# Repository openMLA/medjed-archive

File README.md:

The **Medjed** maskless lithography aligner is part of the openMLA series of photolithography equipment. 

>  **🏗️ Construction in progress**
> A lot is still being worked on for this system. Hardware is being tested and performance will need to be evaluated before people will be able to build their own system. 

### Overview

The MEDJED system is a photolithography system - this means its primary function is to expose a (flat-ish) substrate to patterened light. The substrate will need to be coated in a layer of light-sensitive material known as photoresist. This resist layer in turn will undergo chemical reactions upon exposure to UV light, either rendering areas that were exposed soluble or insoluble to a (liquid) chemical developer. After development of the exposed photoresist layer, some areas of the substrate will remain coated in the photoresist, while others will be free of it. This is the starting point for further patterning steps and is the backbone of modern microfabrication.

The MEDJED system targets a 5um pixel size in its current design. The total project cost is targeted to be 2000-2500 euro. 

There are 3 kinds of documentation for the project:

1. Documentation within this git repository. This is primarily for information about the repository contents.
2. [The project wiki](https://github.com/openMLA/Medjed/wiki). This is for a high level overview of the project, and more in-depth worked out ideas and theory.
3. [The GitHub discussions page](https://github.com/openMLA/Medjed/discussions). This is where small updates, prototypes, and failures are logged. If you have any ideas or comments, you can leave them there! 

### 🙋‍♂️Contributions

Currently the project development is in volatile waters; a lot is still changing and being tested. If you find the project very interesting and think you have some expertise in the relevant areas (e.g. optics, mechanics, machine safety, PCB design) feel free to reach out so we can see if we can divide up some tasks or if you can share some insight/critique into some of the current design layout!

If you are just interesting in trying out the system, or even just trying out some of the assemblies (e.g. just the Z-axis), your feedback and comments on the design files, practicalities and documentation are also very welcome. You can leave comments and propose new ideas in [the GitHub discussions page](https://github.com/openMLA/Medjed/discussions).

### 📃 Current component selection

Below are some of the current components selected for the machine. They may change at any point and are not necessarily the best for the job.  Still, you may find some of them interesting components for your own project.

🔗 More detailed discussion of components choices will be put in the wiki 📑.

Some highlighted components below

* XYZ axis: Snapmaker linear rails (not accurate enough for direct positioning)
* UV patterning: modified DMD projection unit from the Anycubic Photon Ultra DLP printer. See [this blog post for pictures and background](https://nemoandrea.github.io/blog/Anycubic_DLP_teardown/).
* Main optic: [Olympus Plan N 10X 0.25NA](https://www.edmundoptics.com/f/olympus-plan-achromatic-objectives/14535/).  Alternatively, [a cheaper version with the same optical design is produced in China](https://www.astroshop.eu/for-microscopes/evident-olympus-plcn10x-0-25-plan-achromat-objective/p,49913) by Olympus (part:N4239000) which should work just as well. 
* Encoders: [RLS RLC2IC magnetic encoder](https://www.rls.si/eng/rlc2ic-miniature-linear-and-rotary-pcb-level-incremental-magnetic-encoder) - 244nm spec, 2MHz
* Motion controller IC: [TMC4361A](https://www.trinamic.com/fileadmin/assets/Products/ICs_Documents/TMC4361_Datasheet_Rev3.10.pdf)
* Microcontroller: [Teensy 4.1](https://www.pjrc.com/store/teensy41.html)
* Cameras: Raspberry Pi global shutter and HQ camera

### BOM

Consult the [BOM.csv](BOM.csv) for a  complete-ish list of components (note that it is 🏗). The BOM has optional elements.  This allows construction of cheaper versions of MEDJED if certain features are not needed. Some clarification on what the optional modules correspond to:

* WLM: White Light Module: a white light reflection microscope module that allows for inspection of sample after fabrication (image stitching and such)
* BSA: Back Side Alignment: basic camera and optics that allows for backside alignment of substrates
* EXTRA: Catch-all for nice items to have on the system (extra safety switches or extra visual indicators etc), but are not needed for any new functionality.
* ALT: components that can serve as backup for another, preferred, components in the BOM. 

The main BOM in the repository home is aggregated from subassembly BOM's. So you want to look at the components for a subassembly, simply go to the assembly and open the BOM there. [A simple utility function](utils/bom-merger.py) combines the BOMs.

### 👏 Funding Sources

The project is partially funded by the [Delft Open Hardware organisation](https://www.tudelft.nl/en/open-hardware), and the funding made available to them by the [Delft University of Technology](https://www.tudelft.nl/) for the support of open hardware development. Their support has enabled sourcing of components and has been a big enabling factor for the project development, and the project developers are grateful for their support.

### 🛠 Design Tools

Hardware parts are designed in [FreeCAD](https://www.freecad.org/)

PCBs are designed in [KiCAD](https://www.kicad.org/)

Art/Design is generated by Affinity Designer and [Inkscape](https://inkscape.org/).

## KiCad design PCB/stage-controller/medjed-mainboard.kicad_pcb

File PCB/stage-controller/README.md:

## Medjed mainboard

Notes about the mainboard/stage controller for the medjed MLA system.

The current PCB aims to drive the `TMC2209` in the linear axes by combining a `TMC424` (encoder) and `TMC429` (motioncontroller). The datasheet for the `TMC424` is really quite poor however, and the product seems a bit of an afterthought by Trinamic.

The board will probably be redesigned around the `TMC4361A` (one for each axis).  

### Power considerations

The snapmaker linear axes use 24V supply. The snapmaker power supply comes with plenty of overhead in terms of power (as it need to be able to run a 3D printer heated bed) so that is not a concern. 

We also need 5V and 3.3V supply on the board.

5V:

* Teensy 4.1: 100mA
* [3X] RLC2IC encoders: <30mA (no termination resistors) or <130mA with 120ohm termination.
* [3X] AM26LS32A: max 70mA, typ 50mA

3.3V:

* TMC424: 1.5mA
* TMC429: 10mA (running in 3.3V CMOS mode)
* (for future revision: IMXRT60: 53mA)

1.5V:

* TMC424: 10.5mA

### Other

The documentation for `TMC424` does not list a MISO connection to the `TMC429`. It may not be necessary as the information encoded in the Datagrams is precisely the part handled by the `TMC424` (i.e.). Still it might be useful for reading back the state of registers which I don't believe is possible through the `TMC424`. For now I have handled it with a solder jumper.

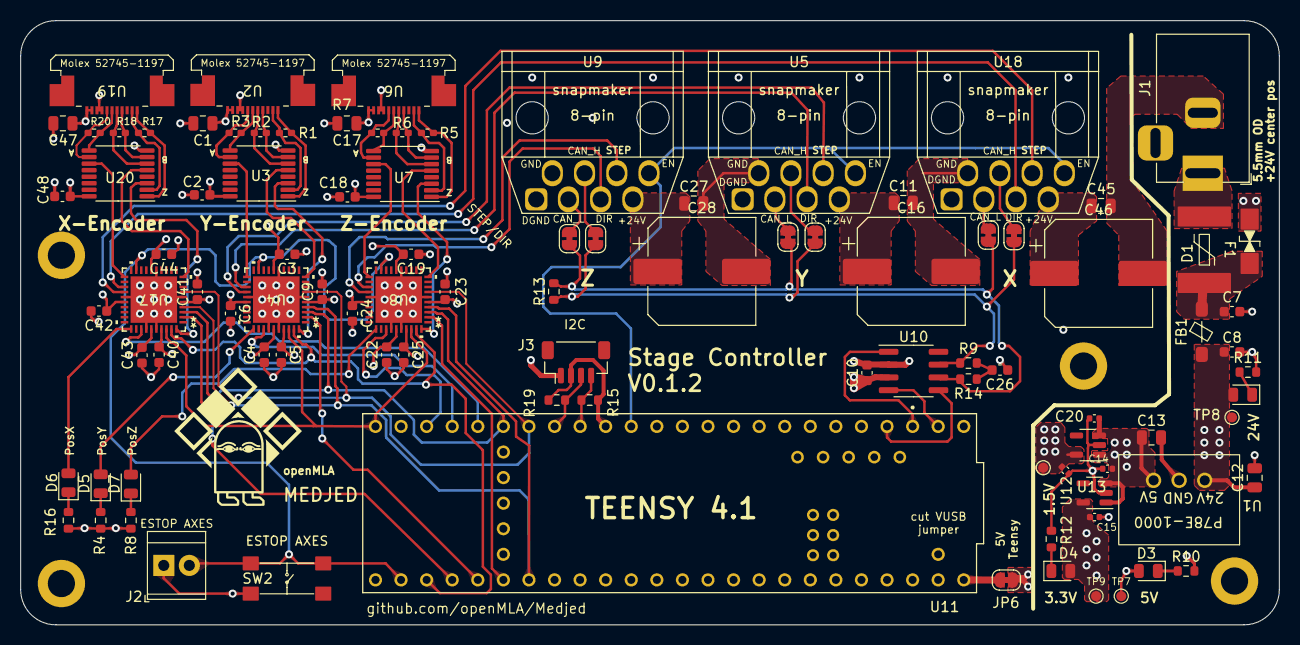
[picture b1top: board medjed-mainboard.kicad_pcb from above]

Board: 4 copper layers, 125.0 x 60.0 mm, 98 parts (0 on the bottom side), 78 nets.

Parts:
C1, C11, C12, C17, C27, C45, C47: 10uF; C_0805_2012Metric
C2, C3, C4, C5, C6, C7, C8, C9, C10, C18, C19, C22, C23, C24, C25, C40, C41, C42, C43, C44, C48: 100nF; C_0603_1608Metric
C13: 22uF; C_0805_2012Metric
C14, C15, C20, C21: 1uF; C_0402_1005Metric
C16, C28, C46: 220uF; CP_Elec_220uf
C26: 4.7nF; C_0603_1608Metric
D1: SMAJ28CA
D2, D3, D4, D5, D6, D7: Red; LED_0805_2012Metric
F1: SMDC185F/33-2; SMDC185F_33-2
FB1: FerriteBead; BLM41P600S
J1: Barrel_Jack; BarrelJack_Horizontal
J2: ESTOP terminal; TerminalBlock_TE_282834-2_1x02_P2.54mm_Horizontal
J3: Conn_01x04_Pin; JST_SH_BM04B-SRSS-TB_1x04-1MP_P1.00mm_Vertical
JP1, JP2, JP3, JP4, JP5, JP6, JP7: SolderJumper_2_Bridged; SolderJumper-2_P1.3mm_Bridged_RoundedPad1.0x1.5mm
R1, R2, R3, R5, R6, R7, R17, R18, R20: 120; R_0402_1005Metric_Pad0.72x0.64mm_HandSolder
R4, R8, R10, R11, R12, R15, R16, R19: 5k1; R_0603_1608Metric
R9, R14: 60.4; R_0603_1608Metric
R13: 120; R_0603_1608Metric
SW2: ESTOP switch; E-switch-button
TP7, TP8, TP9, TP10: TestPoint; TestPoint_Pad_D1.0mm
U1: P78E-1000
U2, U6, U19: Molex 52745-1197
U3, U7, U20: TSSOP-16-AM26LS32A
U4, U8, U17: TMC4361A-LA; TMC4361A_QFN40_6X6_TRI
U5, U9, U18: snapmaker_8-pin
U10: TCAN330; SOIC-8_3.9x4.9mm_P1.27mm
U11: teensy 4.1; teensy_4.1
U12: MIC5317-3.3; SOT-23-5
U13: MIC5317-1.8; SOT-23-5

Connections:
+1V8: C3.2, C4.2, C19.2, C21.1, C22.2, C43.2, C44.2, TP10.1, U4.16 (VDD1V8), U4.35 (VDD1V8), U8.16 (VDD1V8), U8.35 (VDD1V8), U13.5 (Vout), U17.16 (VDD1V8), U17.35 (VDD1V8)
+3.3V: C5.1, C6.1, C9.1, C10.1, C15.1, C23.1, C24.1, C25.1, C40.1, C41.1, C42.1, D4.2 (A), TP9.1, U4.5 (VCC), U4.26 (VCC), U4.37 (VCC), U8.5 (VCC), U8.26 (VCC), U8.37 (VCC), U10.3 (VCC), U12.5 (Vout), U17.5 (VCC), U17.26 (VCC), U17.37 (VCC)
+5V: C1.1, C2.1, C13.1, C14.1, C17.1, C18.1, C20.1, C47.1, C48.1, D3.2 (A), JP6.2 (B), TP7.1, U1.3 (Vout), U2.1 (+5V), U2.2 (+5V), U3.16 (Vcc), U6.1 (+5V), U6.2 (+5V), U7.16 (Vcc), U12.1 (Vin), U12.3 (EN), U13.1 (Vin), U13.3 (EN), U19.1 (+5V), U19.2 (+5V), U20.16 (Vcc)
+24V: C8.1, C11.1, C12.1, C16.1, C27.1, C28.1, C45.1, C46.1, D2.2 (A), FB1.2, TP8.1, U1.1 (Vin), U5.7 (+24V), U9.7 (+24V), U18.7 (+24V)
/+3.3V Teensy: J3.2, R15.1, R19.1, U11.3.3V_1 (3.3V), U11.3.3V_2 (3.3V), U11.3.3V_3 (3.3V)
/+24Vfused: C7.1, D1.2 (A2), F1.2, FB1.1
/+24Vsrc: F1.1, J1.1
/Axis X/A: U17.40 (A), U20.3 (1Y)
/Axis X/B: U17.10 (B), U20.5 (2Y)
/Axis X/CAN_H: JP5.1 (A), U18.4 (CAN_H)
/Axis X/CAN_L: JP7.1 (A), U18.3 (CAN_L)
/Axis X/DIR: U17.23 (DIROUT_PWMB), U18.5 (DIR)
/Axis X/N: U17.21 (N), U20.11 (3Y)
/Axis X/STEP: U17.24 (STPOUT_PWMA), U18.6 (STEP)
/Axis X/TGT: D6.2 (A), U17.31 (TARGET_REACHED)
/Axis X/Z_A+: R20.2, U19.5 (A+), U20.10 (3A)
/Axis X/Z_A-: R20.1, U19.6 (A-), U20.9 (3B)
/Axis X/Z_B+: R18.2, U19.7 (B+), U20.6 (2A)
/Axis X/Z_B-: R18.1, U19.8 (B-), U20.7 (2B)
/Axis X/Z_Z+: R17.2, U19.10 (Z+), U20.2 (1A)
/Axis X/Z_Z-: R17.1, U19.11 (Z-), U20.1 (1B)
/Axis Y/A: U3.3 (1Y), U4.40 (A)
/Axis Y/B: U3.5 (2Y), U4.10 (B)
/Axis Y/CAN_H: JP4.1 (A), U5.4 (CAN_H)
/Axis Y/CAN_L: JP3.1 (A), U5.3 (CAN_L)
/Axis Y/DIR: U4.23 (DIROUT_PWMB), U5.5 (DIR)
/Axis Y/N: U3.11 (3Y), U4.21 (N)
/Axis Y/STEP: U4.24 (STPOUT_PWMA), U5.6 (STEP)
/Axis Y/TGT: D5.2 (A), U4.31 (TARGET_REACHED)
/Axis Y/Z_A+: R3.2, U2.5 (A+), U3.10 (3A)
/Axis Y/Z_A-: R3.1, U2.6 (A-), U3.9 (3B)
/Axis Y/Z_B+: R2.2, U2.7 (B+), U3.6 (2A)
/Axis Y/Z_B-: R2.1, U2.8 (B-), U3.7 (2B)
/Axis Y/Z_Z+: R1.2, U2.10 (Z+), U3.2 (1A)
/Axis Y/Z_Z-: R1.1, U2.11 (Z-), U3.1 (1B)
/Axis Z/A: U7.3 (1Y), U8.40 (A)
/Axis Z/B: U7.5 (2Y), U8.10 (B)
/Axis Z/CAN_H: JP1.1 (A), U9.4 (CAN_H)
/Axis Z/CAN_L: JP2.1 (A), U9.3 (CAN_L)
/Axis Z/DIR: U8.23 (DIROUT_PWMB), U9.5 (DIR)
/Axis Z/N: U7.11 (3Y), U8.21 (N)
/Axis Z/STEP: U8.24 (STPOUT_PWMA), U9.6 (STEP)
/Axis Z/TGT: D7.2 (A), U8.31 (TARGET_REACHED)
/Axis Z/Z_A+: R7.2, U6.5 (A+), U7.10 (3A)
/Axis Z/Z_A-: R7.1, U6.6 (A-), U7.9 (3B)
/Axis Z/Z_B+: R6.2, U6.7 (B+), U7.6 (2A)
/Axis Z/Z_B-: R6.1, U6.8 (B-), U7.7 (2B)
/Axis Z/Z_Z+: R5.2, U6.10 (Z+), U7.2 (1A)
/Axis Z/Z_Z-: R5.1, U6.11 (Z-), U7.1 (1B)
/SCL: J3.4, R15.2, U11.24 (A10)
/SDA: J3.3, R19.2, U11.25 (A11)
CAN_EN: U10.5 (SHDN), U11.2 (OUT2)
CAN_H: JP1.2 (B), JP4.2 (B), JP5.2 (B), R9.1, R13.1, U10.7 (CANH)
CAN_L: JP2.2 (B), JP3.2 (B), JP7.2 (B), R13.2, R14.2, U10.6 (CANL)
CS_X: U11.36 (CS2), U17.2 (NSCSIN)
CS_Y: U4.2 (NSCSIN), U11.37 (CS3)
CS_Z: U8.2 (NSCSIN), U11.38 (A14)
EN_SNAP: U5.8 (EN), U9.8 (EN), U11.12 (MISO), U18.8 (EN)
ESTOP: J2.2, SW2.3 (K), SW2.4 (A), U4.19 (NFREEZE), U8.19 (NFREEZE), U11.34 (RX8), U17.19 (NFREEZE)
GND: C1.2, C2.2, C3.1, C4.1, C5.2, C6.2, C7.2, C8.2, C9.2, C10.2, C11.2, C12.2, C13.2, C14.2, C15.2, C16.2, C17.2, C18.2, C19.1, C20.2, C21.2, C22.1, C23.2, C24.2, C25.2, C26.1, C27.2, C28.2, C40.2, C41.2, C42.2, C43.1, C44.1, C45.2, C46.2, C47.2, C48.2, D1.1 (A1), J1.2, J2.1, J3.1, R4.2, R8.2, R10.2, R11.2, R12.2, R16.2, SW2.1, U1.2 (GND), U2.3 (GND), U2.4 (GND), U3.8 (GND), U4.6 (GND), U4.15 (GND), U4.25 (GND), U4.34 (TEST_MODE), U4.36 (GND), U4.41 (GND), U5.1 (DGND), U5.2 (GND), U6.3 (GND), U6.4 (GND), U7.8 (GND), U8.6 (GND), U8.15 (GND), U8.25 (GND), U8.34 (TEST_MODE), U8.36 (GND), U8.41 (GND), U9.1 (DGND), U9.2 (GND), U10.2 (GND), U11.GND1 (GND), U11.GND2 (GND), U11.GND3 (GND), U11.GND4 (GND), U11.GND5 (GND), U12.2 (GND), U13.2 (GND), U17.6 (GND), U17.15 (GND), U17.25 (GND), U17.34 (TEST_MODE), U17.36 (GND), U17.41 (GND), U18.1 (DGND), U18.2 (GND), U19.3 (GND), U19.4 (GND), U20.8 (GND)
INT_X: U11.28 (RX7), U17.33 (INTR)
INT_Y: U4.33 (INTR), U11.29 (TX7)
INT_Z: U8.33 (INTR), U11.30 (CRX3)
MISO: U4.4 (SDIIN), U8.4 (SDIIN), U11.39 (A15), U17.4 (SDIIN)
MOSI: U4.7 (SDOIN), U8.7 (SDOIN), U11.26 (A12), U17.7 (SDOIN)
unnamed: C26.2, R9.2, R14.1
unnamed: D2.1 (K), R11.1
unnamed: D3.1 (K), R10.1
unnamed: D4.1 (K), R12.1
unnamed: D5.1 (K), R4.1
unnamed: D6.1 (K), R16.1
unnamed: D7.1 (K), R8.1
unnamed: JP6.1 (A), U11.VIN
unnamed: U10.4 (RXD), U11.0 (RX1)
unnamed: U10.1 (TXD), U11.1 (TX1)
RST_AXES: U4.39 (NRST), U8.39 (NRST), U11.35 (TX8), U17.39 (NRST)
SCK: U4.3 (SCKIN), U8.3 (SCKIN), U11.27 (A13), U17.3 (SCKIN)
TeensyCLK: U4.38 (CLK_EXT), U8.38 (CLK_EXT), U11.32 (OUT1B), U17.38 (CLK_EXT)

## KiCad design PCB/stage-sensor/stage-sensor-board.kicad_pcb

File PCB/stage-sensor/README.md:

## Chuck Sensor PCB

This PCB is designed to fit into the sample chuck of the MEDJED system. It contains the following 3 sensors:

* A temperature and humidity sensor
* An accelerometer and gyroscope 
* A UV sensor

### UV sensor

The OPT3002 Light sensor will be useful to calibrate and correct for UV intensity of the illumination and projection system. The sensing area is smaller than the projected area, so some stage movement and averaging tricks will have to be applied. 

Some fiducial crosses and silkscreen markings have been added to help automation efforts and the finding of the IC when manually moving the stage around

### Temperature and Humidity sensor

The SHT45 temperature and humidity sensor is just for logging purposes. Changes in temperature and humidity can affect the photoresist and development process, so having a record of this is useful.

### Accelerometer and Gyroscope

The ICM42605 accelerometer and gyroscope unit can serve two purposes:

1. Get a feel for stage movement and apply input shaping to increase movement and settling speed (low priority)
2. Determine when the stage has settled and we are ready to expose an image.

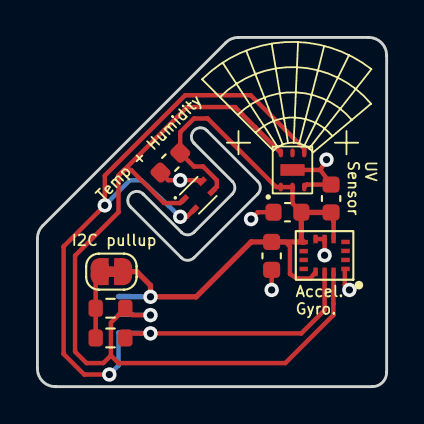
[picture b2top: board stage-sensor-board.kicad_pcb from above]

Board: 2 copper layers, 19.4 x 19.4 mm, 11 parts (1 on the bottom side), 5 nets.

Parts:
C3: 10nF; C_0603_1608Metric
C4: 2.2uF; C_0603_1608Metric
C5, C6: 100nF; C_0603_1608Metric
J1: STEMMA QT; JST_SH_BM04B-SRSS-TB_1x04-1MP_P1.00mm_Vertical
JP1: Bridged; SolderJumper-2_P1.3mm_Bridged_RoundedPad1.0x1.5mm
R1, R2: 11K; R_0603_1608Metric
U1: ICM 42605; icm-42605
U2: OPT3002
U3: SHT45; SHT4X

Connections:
+3.3V: C3.1, C4.1, C5.2, C6.2, J1.2, JP1.2 (B), U1.5 (VDDIO), U1.8 (VDD), U1.12 (AP_CS), U2.1 (VDD), U2.2 (ADDR), U3.3 (VDD)
/I2C_pullup: JP1.1 (A), R1.1, R2.1
/SCL: J1.4, R2.2, U1.13 (SCL), U2.4 (SCL), U3.2 (SCL)
/SDA: J1.3, R1.2, U1.14 (SDA), U2.6 (SDA), U3.1 (SDA)
GND: C3.2, C4.2, C5.1, C6.1, J1.1, U1.1 (I2C_addr), U1.6 (GND), U1.7 (GND), U2.3 (GND), U3.4 (VSS)

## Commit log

2023-03-11 Initial documentation
    Add initial documentation and some basic freeCAD files as a sample.
2023-04-07 Stage controller PCB schematic
    Add most of the components for the stage controller in place. Nothing routed up yet, only working on the schematic and footprints.
2023-04-16 Update freecad files with assemblies
    Add new parts and combine existing parts with assembly 4 workbench in FreeCAD
2023-04-20 Add wiki as submodule
2023-04-29 Add initial version stage PCB
    Will probably need major revisions as efforts towards TMC4361A will require significant changes.
2023-04-29 Update stage-PCB schematic
2023-05-06 New TMC4361 design
    Redesigned stage controller around the TMC4361.
2023-05-07 Finalise part numbers and I2C pullup
    Complete mouser part numbers. Added pullup for I2C connector.
2023-05-19 Update docs
2023-05-21 Add enclosure files
    Add initial design for an enclosure for the the Medjed system. More work is needed for the main door and interlock.
2023-05-21 stage controller PCB version 0.1.2
    Versino of stage controller produced by Aisler pending testing. Added some 3D models for board visualisation.
2023-05-27 Near Final Enclosure design
    Added door and printed parts design for enclosure. Will need verification by building and cable routing through printed skirting.
2023-05-27 Fix image
    Fixed image for enclosure documentation
2023-05-29 Add early optical design
2023-06-03 Add licence
    Somehow I did not have a licence yet...
2023-06-03 Update main readme
    Changed the banner to be easier to look at in dark mode. Expanded documentation.
2023-06-13 Update enclosure for new double-z layout
    Updated enclosure for the new double z axis layout. Functionally still identical.
2023-06-13 Reorganisation and new assembly images
    Not all files are pushed yet to keep the repository size in check, but new preview of the design is present in the main readme.
2023-06-15 Add bom-merger utility
    Simple utility to allow BOMs to be split up between subassemblies. Added two quick demo CSV files to drive the idea home.
2023-06-16 Add subassembly BOMs and update utility
    Filled in the BOMs for subassemblies and improved the bom-merger utilities with more capabilities such as optional categories and template filtering.
2023-06-30 Update main readme with funding & discussions
    Add funding information and highlight the use of GitHub discussions.
2023-07-01 Add designs for linear-rail+stepper Z-axis
    new Z-axis for focussing.
2023-07-01 Update BOMs with Z-focus assembly
2023-07-04 Update enclosure with print-in-place hinges
    Cleaned up directory and added dxf for for easy ordering.
2023-09-18 Reorganise the sample stage and update design
    Renamed the sample chuck to be more descriptive. Revising the design to be more compact and for resin printing.
2023-09-24 Add basic 45 degree cage mount optic holder
    Basic design that complements the tip-tilt holder for basic designs and prototyping
2023-09-24 Add linear rail based z-positioner
    Added designs and basic documentation for a linear-rail based z focus mechanism.
2023-09-24 Fix: add freecad file for 45 deg cage bracket
    Forgot to include the freecad file for commit f51dc9b. Did some housekeeping and removed old files that are no longer relevant.
2023-09-24 Add sample chuck PCB
    Design files for a new PCB that sits inside the sample chuck. New sample chuck design not yet commited.
2023-10-07 Add inline tip-tilt design
    New cage element, a 1-inch tip-tilt lens holder. Prototype discussed in https://github.com/openMLA/Medjed/discussions/14
2023-10-07 Update freecad optics readme
    Correct missing image and description
2023-10-21 Update main assembly image
    Update the current assembly image with new optical developments.
2023-10-28 Add simple jpg preview script
    Minimise size of repository while still including preview images.
2023-10-28 Add submodule: assembly
    Add the git-annex managed assembly files as a submodule
2023-10-28 Prepare PCB for submodule mode
2023-10-28 Update assembly submodule version
    Important version bump
2023-10-29 Update PCB files
    Pre-removal and submodule reorganisation
2023-10-29 Remove PCB directory
    In preparatiof of submodule introduction
2023-10-29 Add PCB back as submodule
    Return of the PCB directory but now as a submodule.
2023-10-29 Add final freecad files to clean up directory
    Prior to removal
2023-10-29 Remove freecad files from directory
    Will rebase directory in the future to remove this bloat. Files can still be found in submodule.
2023-10-29 Final information before rebase and archival
